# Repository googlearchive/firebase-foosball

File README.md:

# Status: Archived
This repository has been archived and is no longer maintained.

Firebase Foosball
=================

The hardware bit for building an internet connected Foosball table.

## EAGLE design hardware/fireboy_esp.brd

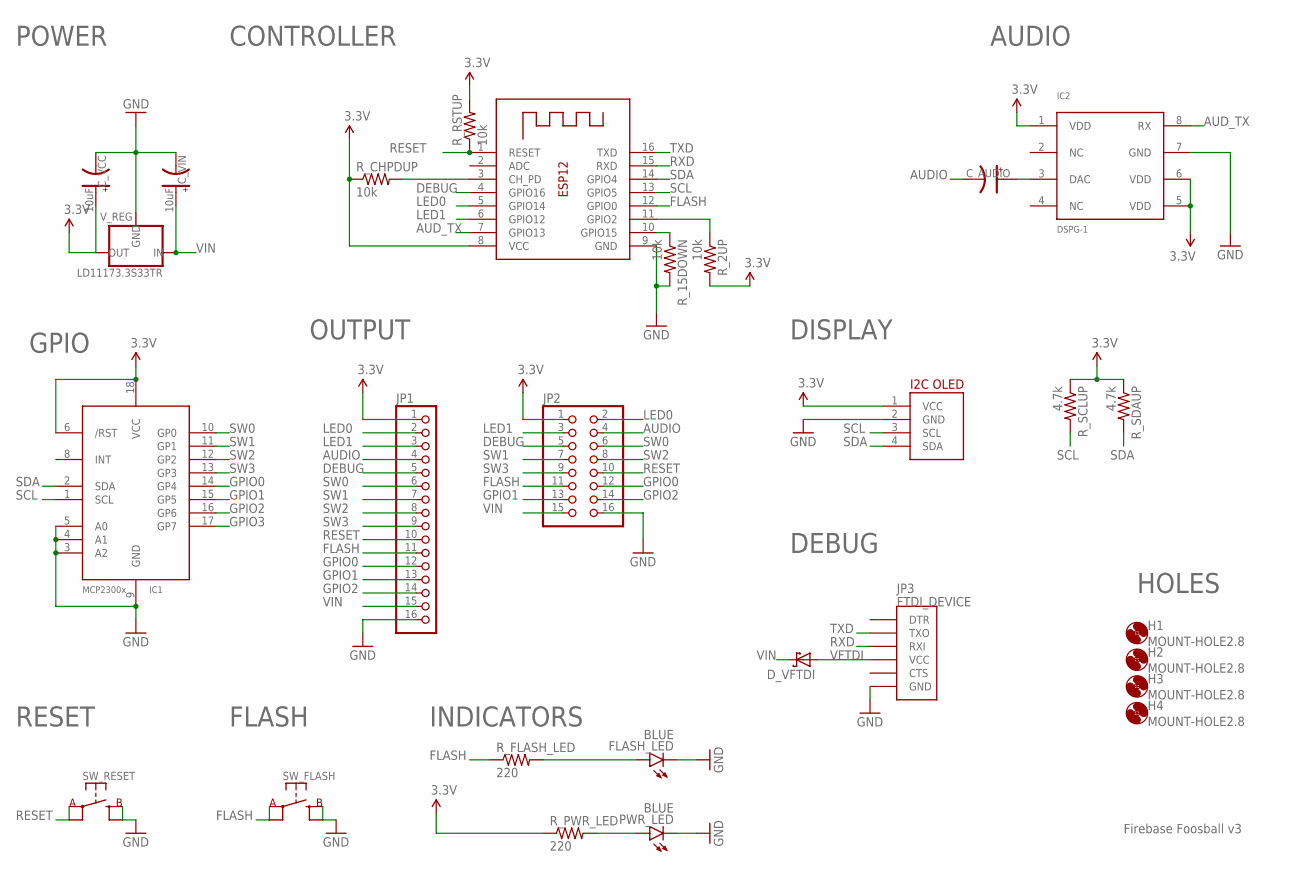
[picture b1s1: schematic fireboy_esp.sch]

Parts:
C_AUDIO: CAP-POL025X50; CAP-POL-025X50
C_VCC: 10uF; CAP-POL-025X50
C_VIN: 10uF; CAP-POL-025X50
D_VFTDI: SCHOTTKY-DIODEDO41; DO41-10
FLASH_LED: BLUE; LED3MM
H1, H2, H3, H4: MOUNT-HOLE2.8; 2,8
IC0: ESP-12
IC1: MCP23008/P; DIL18
IC2: DSPG-1; DIL08
JP1: PINHD-1X16; 1X16
JP2: PINHD-2X8; 2X08
JP3: FTDI_DEVICE; FTDI_DEVICE_SIDE
PWR_LED: BLUE; LED3MM
R_2UP, R_15DOWN: 10k; AXIAL-0.3
R_CHPDUP: 10k; AXIAL-0.3
R_FLASH_LED: 220; AXIAL-0.3
R_PWR_LED: 220; AXIAL-0.3
R_RSTUP: 10k; AXIAL-0.3
R_SCLUP: 4.7k; AXIAL-0.3
R_SDAUP: 4.7k; AXIAL-0.3
SW_FLASH: SW-SPSTTH06X06; SW-SPST-TH06X06
SW_RESET: SW-SPSTTH06X06; SW-SPST-TH06X06
U$2: I2C_OLED; I2C_OLED_PACKAGE
V_REG: LD11173.3S33TR; SOT223

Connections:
3.3V: IC1.6 (/RST), IC1.18 (VCC), IC2.1 (VDD), IC2.5 (VDD), IC2.6 (VDD), JP1.1, JP2.1, R_2UP.P$2 (2), R_PWR_LED.P$1 (1), R_RSTUP.P$2 (2), R_SCLUP.P$1 (1), R_SDAUP.P$1 (1), U$2.1 (VCC)
AUDIO: C_AUDIO.C, JP1.4, JP2.4
AUD_TX: IC0.7 (GPIO13), IC2.8 (RX)
DEBUG: IC0.4 (GPIO16), JP1.5, JP2.5
FLASH: IC0.12 (GPIO0), JP1.11, JP2.11, R_FLASH_LED.P$1 (1), SW_FLASH.A@1 (A)
GND: C_VCC.C, C_VIN.C, FLASH_LED.K (C), IC0.9 (GND), IC1.3 (A2), IC1.4 (A1), IC1.5 (A0), IC1.9 (GND), IC2.7 (GND), JP1.16, JP2.16, JP3.P$6 (GND), PWR_LED.K (C), R_15DOWN.P$2 (2), SW_FLASH.B@1 (B), SW_RESET.B@1 (B), U$2.2 (GND), V_REG.1 (GND)
GPIO0: IC1.14 (GP4), JP1.12, JP2.12
GPIO1: IC1.15 (GP5), JP1.13, JP2.13
GPIO2: IC1.16 (GP6), JP1.14, JP2.14
GPIO3: IC1.17 (GP7)
LED0: IC0.5 (GPIO14), JP1.2, JP2.2
LED1: IC0.6 (GPIO12), JP1.3, JP2.3
unnamed: IC0.11 (GPIO2), R_2UP.P$1 (1)
unnamed: IC0.10 (GPIO15), R_15DOWN.P$1 (1)
unnamed: IC0.3 (CH_PD), R_CHPDUP.P$2 (2)
unnamed: FLASH_LED.A, R_FLASH_LED.P$2 (2)
unnamed: PWR_LED.A, R_PWR_LED.P$2 (2)
unnamed: C_VCC.A, V_REG.2 (OUT), V_REG.4 (OUT)
unnamed: C_AUDIO.A, IC2.3 (DAC)
RESET: IC0.1 (RESET), JP1.10, JP2.10, R_RSTUP.P$1 (1), SW_RESET.A@1 (A)
RXD: IC0.15 (RXD), JP3.P$3 (RXI)
R_CHPDUP: IC0.8 (VCC), R_CHPDUP.P$1 (1)
SCL: IC0.13 (GPIO5), IC1.1 (SCL), R_SCLUP.P$2 (2), U$2.3 (SCL)
SDA: IC0.14 (GPIO4), IC1.2 (SDA), R_SDAUP.P$2 (2), U$2.4 (SDA)
SW0: IC1.10 (GP0), JP1.6, JP2.6
SW1: IC1.11 (GP1), JP1.7, JP2.7
SW2: IC1.12 (GP2), JP1.8, JP2.8
SW3: IC1.13 (GP3), JP1.9, JP2.9
TXD: IC0.16 (TXD), JP3.P$2 (TXO)
VFTDI: D_VFTDI.A, JP3.P$4 (VCC)
VIN: C_VIN.A, D_VFTDI.C, JP1.15, JP2.15, V_REG.3 (IN)

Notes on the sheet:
POWER
RESET
FLASH
CONTROLLER
GPIO
DEBUG
DISPLAY
AUDIO
OUTPUT
INDICATORS
HOLES
Firebase Foosball v3

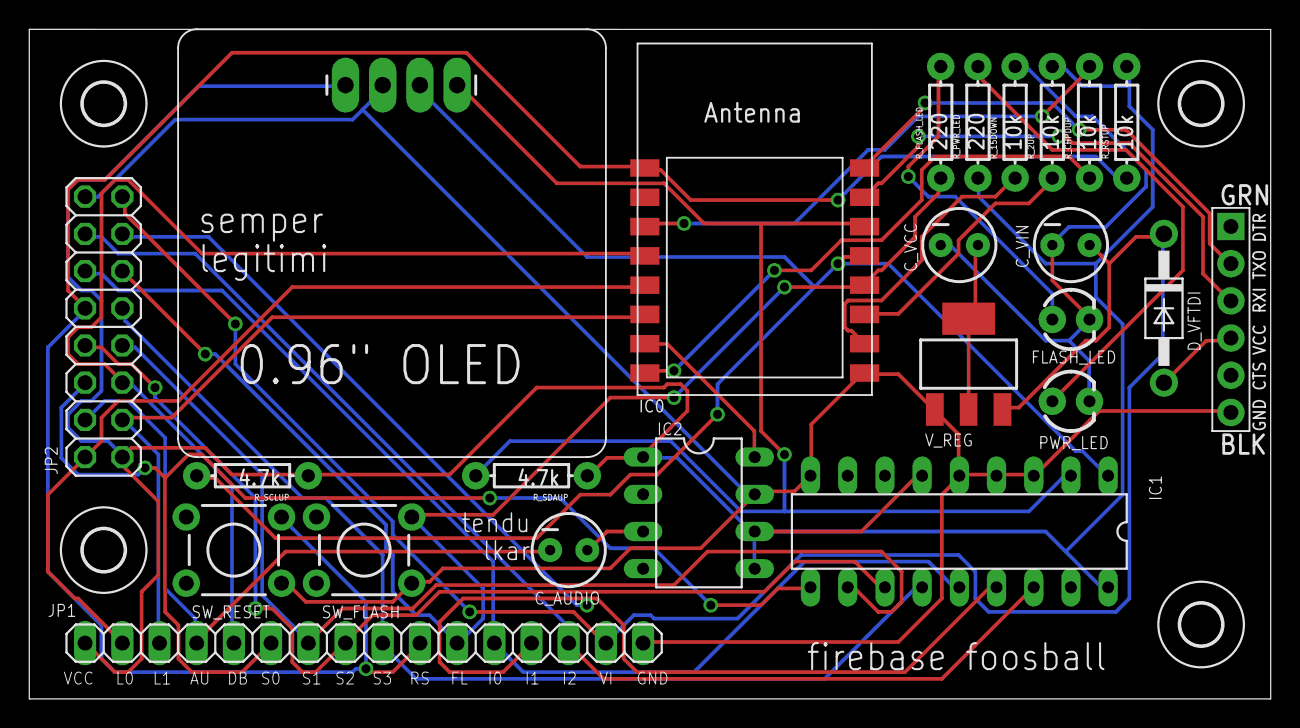
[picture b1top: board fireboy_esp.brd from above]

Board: 2 copper layers, 84.8 x 45.7 mm, 28 parts (0 on the bottom side), 30 nets.

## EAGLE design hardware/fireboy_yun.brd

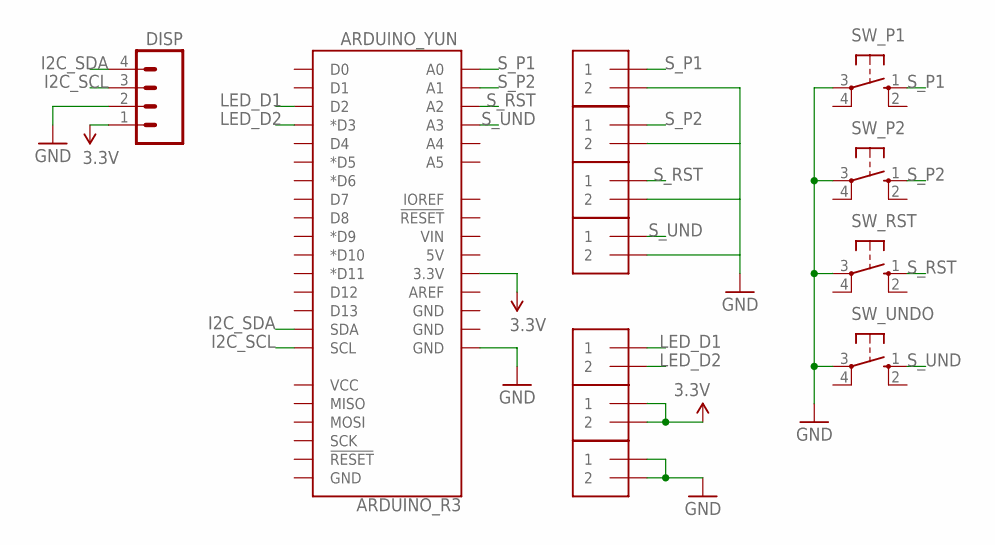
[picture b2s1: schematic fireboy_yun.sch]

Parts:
ARDUINO_YUN: ARDUINO_R3
DISP: M04PTH; 1X04
LED_3.3V: 1X2-3.5MM
LED_DATA: 1X2-3.5MM
LED_GND: 1X2-3.5MM
SW_P1, SW_P2: 40-XX; B3F-40XX
SW_RST: 40-XX; B3F-40XX
SW_UNDO: 40-XX; B3F-40XX
S_P1, S_P2: 1X2-3.5MM
S_RST: 1X2-3.5MM
S_UND: 1X2-3.5MM

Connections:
3.3V: ARDUINO_YUN.3.3V, DISP.1, LED_3.3V.1, LED_3.3V.2
GND: ARDUINO_YUN.GND@2 (GND), DISP.2, LED_GND.1, LED_GND.2, SW_P1.3, SW_P2.3, SW_RST.3, SW_UNDO.3, S_P1.2
I2C_SCL: ARDUINO_YUN.SCL, DISP.3
I2C_SDA: ARDUINO_YUN.SDA, DISP.4
LED_D1: ARDUINO_YUN.D2, LED_DATA.1
LED_D2: ARDUINO_YUN.D3 (*D3), LED_DATA.2
S_P1: ARDUINO_YUN.A0, SW_P1.1 (S), S_P1.1
S_P2: ARDUINO_YUN.A1, S_P2.1
S_RST: ARDUINO_YUN.A2, S_RST.1
S_UND: ARDUINO_YUN.A3, S_UND.1

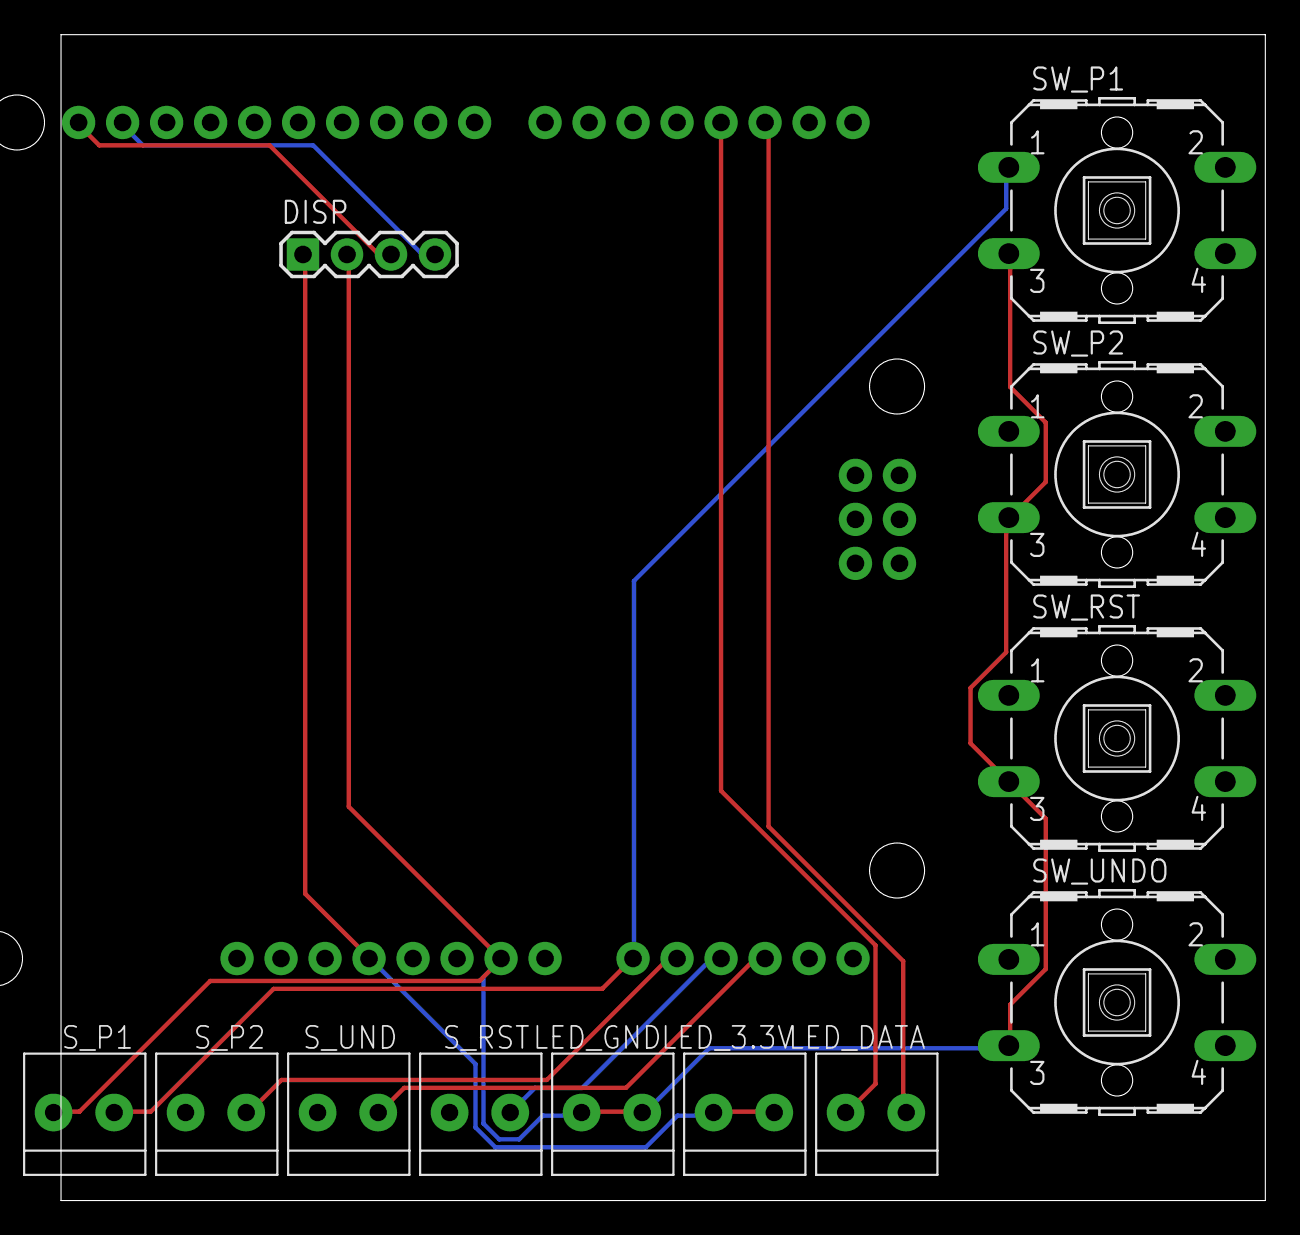
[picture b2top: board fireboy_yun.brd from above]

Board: 2 copper layers, 69.5 x 67.3 mm, 13 parts (0 on the bottom side), 10 nets.

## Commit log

2016-05-12 Initial import.
2016-05-12 legalese
2016-05-12 Add the board IDs
2016-05-13 More sync fixes and better animations.
2016-05-14 Last version before moving to listneing on the yun
2016-05-23 Prod cut for I/O
2018-08-24 Prepare for archiving (#1)
    * Prepare for archiving
    * Line break

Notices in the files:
parts and their libraries:
SparkFun-LED: Licensing: Creative Commons ShareAlike 4.0 International - https://creativecommons.org/licenses/by-sa/4.0
